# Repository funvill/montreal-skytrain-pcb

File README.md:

# montreal-skytrain-pcb

A printed circuit board that is a map of the Montréal Métro, with one
addressable RGB LED per station: all four lines plus the Blue line
extension to Anjou, 73 stations in all. A port of the
[Vancouver SkyTrain PCB](https://github.com/funvill/vancouver-skytrain-pcb).

**Sent to JLCPCB for manufacture on October 18th, 2026.** The files that
were uploaded are in [`manufactured/`](manufactured/)
(`jlcpcb_2026Oct18-191040.zip`, identical to the `2026-10-18-1853` outputs
in [`hardware/jlcpcb/`](hardware/jlcpcb/)).

**Front:** square 160 × 160 mm schematic map with straight lines and rounded
bends, exposed-copper (ENIG gold) water at true scale, silkscreen routes,
station rings and official station names, one XL-1615 WS2812B LED per
station.

**Back:** snowy owl in a tie, Seeed XIAO RP2040 controller (soldered by
hand), pads for four buttons, LED chain and power test points, M3 mounting
holes.

Renders are KiCad 10 `kicad-cli pcb render` output (`tools/render_board.py`).

## Where things are

| Folder | What |
|---|---|
| [`hardware/`](hardware/) | KiCad 10 project; [`hardware/README.md`](hardware/README.md) covers the board's state, regeneration and checks |
| [`hardware/jlcpcb/`](hardware/jlcpcb/) | Gerbers, BOM and pick-and-place for JLCPCB, and how they were made |
| [`manufactured/`](manufactured/) | The exact package sent to the manufacturer |
| [`input/`](input/) | Station and water data, the map builders, and the hand label placements |
| [`tools/`](tools/) | The pipeline: placement, artwork, labels, routing helpers, checks, outputs |
| [`firmware/`](firmware/) | XIAO RP2040 firmware with the STM line colours |
| [`runbook-new-city.md`](runbook-new-city.md) | How to port the board to another city |
| [`lessons-learned.md`](lessons-learned.md) | What this board and the Vancouver one taught, and the pre-order checklist |

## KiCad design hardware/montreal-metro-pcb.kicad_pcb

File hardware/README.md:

# Hardware (KiCad 10)

`montreal-metro-pcb` — 160 × 160 mm, 2 layers, 73 WS2812B LEDs (XL-1615), one
per station, generated from `../input/montreal-schematic-square.json`.

Copied from the Vancouver SkyTrain v3 project and ported by the scripts in
`../tools`. **The board is placed and has its artwork. It is not routed: routing is done by hand.**

## State

| | |
|---|---|
| Schematic | 73 LEDs. LED69–73 were added by `add_schematic_leds.py`; chain and power verified from KiCad's netlist by `check_led_chain.py` |
| Board vs schematic | 0 parity issues (`kicad-cli pcb drc --schematic-parity`) |
| Placement | LEDs at their stations, each turned so DOUT faces the next LED; 8 capacitors on the front in spots clear of labels, routes and water; XIAO and buttons on the back at (124, 122) mm, away from the downtown LEDs whose vias their pads would block; M3 holes 4 mm in from each corner |
| Bulk capacitor | `C1`, 100 µF 6.3 V X5R 1206 (LCSC C15008, a JLCPCB basic part), on the back at (140, 132.3) mm beside the +5V track from U1 pad 14 to the +5V2 test point. Basic parts have no 100–470 µF electrolytic; the only other basic 100 µF is a 6.3 V tantalum, which is too close to its rating on a 5 V rail. At 5 V the ceramic's DC-bias derating leaves roughly a quarter of its nominal value |
| Data line | `R1`, 330 Ω 0402 (LCSC C25104, basic), in series between U1 pad 8 (`LED_DATA`, also on the `LED_IN1` test point) and LED1 (`LED_IN`), on the front beside the data via at (130.4, 110.5) mm |
| Back artwork | Snowy owl in a tie (`../snowy_owl_tie_pcb_silkscreen.svg`) on B.SilkS as the board-only footprint `LOGO1`: 66.9 × 100 mm, centred, top 2/3 of the board, clear of every back-side part. Regenerate with `svg_to_silk.py` (below) |
| Artwork | Water (bare copper), routes, station rings and labels, wordmark — written by `export_art.py` |
| Labels | Placed by hand in KiCad (2026-10-13) and frozen in `../input/label_overrides-square.json`; every build re-applies them |
| Routing | **None.** The tracks are to be routed by hand. An autorouted version (Freerouting, DRC-clean) is in git history at `b02ee1b` for reference |
| DRC | No clearance, edge, short or courtyard violations; every net is unconnected until routed |
| Back side | The Vancouver moon-phase artwork was removed: it is 191 mm wide and does not fit this board |

## Regenerating

From `../tools`, after any change to the data file:

```
python export_placement.py ../input/montreal-schematic-square.json ../hardware --scale 2.0
python place_parts.py      ../input/montreal-schematic-square.json ../hardware --scale 2.0
python reposition_board.py ../hardware/montreal-metro-pcb.kicad_pcb ../hardware/leds.csv --board 160 --height 160 --controller 124 122
kicad-cli sch export netlist --format kicadsexpr -o ../test-results/netlist.net ../hardware/montreal-metro-pcb.kicad_sch
"C:/Program Files/KiCad/10.0/bin/python.exe" port_board.py ../hardware/montreal-metro-pcb.kicad_pcb ../test-results/netlist.net ../hardware/leds.csv ../hardware/parts.csv
python export_art.py       ../input/montreal-schematic-square.json ../hardware/montreal-metro-pcb.kicad_pcb --scale 2.0
"C:/Program Files/KiCad/10.0/bin/python.exe" mask_under_silk.py ../hardware/montreal-metro-pcb.kicad_pcb
```

Use the same `reposition_board.py` arguments every time, including
`--controller 124 122`.

`mask_under_silk.py` must follow every `export_art.py` run. The water is a
solder-mask opening, and silkscreen cannot print on an opening (JLCPCB clips
it, as does the gerber export's `--subtract-soldermask`), so the routes,
rings and leaders crossing the water would vanish. It closes the opening
0.2 mm around the ink; the copper stays, under mask.

## Routing

Routing is manual. The water is bare copper on the front with no net, so
front-side tracks must not cross it; ground pads on the front each need a
via to the back pour, because the front pour is cut into islands by the
artwork. `U1` pad 13 (GND) sits between two pads closer than the pour's
clearance, so the pour will not reach it: give it a track.

`rebuild_board.sh` leaves tracks alone. `rebuild_board.sh --autoroute`
replaces **every** track with the autorouter's (`autoroute.py`,
`stitch_ground.py`); `autoroute.py clear` removes them all.

## After editing labels in KiCad

```
python import_labels.py ../input/montreal-schematic-square.json ../hardware/montreal-metro-pcb.kicad_pcb
python save_label_overrides.py ../input/montreal-schematic-square.json ../input/label_overrides-square.json
```

Do this before any rebuild, or the exporter writes the old labels back.

`port_board.py` moves LEDs and re-aims them, so once tracks exist, re-running
it after moving a station will leave those tracks behind. Do not pass
`--strip` again: that removes every track and all front artwork.

Or run the whole thing, placement through renders, in one go (Git Bash, from
`../tools`); it does not touch tracks:

```
./rebuild_board.sh
```

## Back artwork

```
"C:/Program Files/KiCad/10.0/bin/python.exe" svg_to_silk.py ../snowy_owl_tie_pcb_silkscreen.svg ../hardware/montreal-metro-pcb.kicad_pcb --ref LOGO1 --height 100 --top 4.5
```

Replaces `LOGO1` in place; the art is mirrored so it reads correctly from the back.

## Checking

```
python check_led_chain.py ../test-results/netlist.net 73
kicad-cli pcb drc ../hardware/montreal-metro-pcb.kicad_pcb -o ../test-results/drc.json --format json --severity-error --severity-warning --schematic-parity --refill-zones --save-board
python render_board.py ../hardware/montreal-metro-pcb.kicad_pcb ../test-results --kicad-cli "C:/Program Files/KiCad/10.0/bin/kicad-cli.exe"
```

## Still to do

1. **Route the board** (by hand).
2. Check U1's orientation (USB-C toward a board edge) and the test-point
   positions on the back.
3. New back-side artwork, if wanted.
5. DRC, then fabrication outputs (`make_jlcpcb.py`). ENIG finish, so the bare
   copper reads gold.

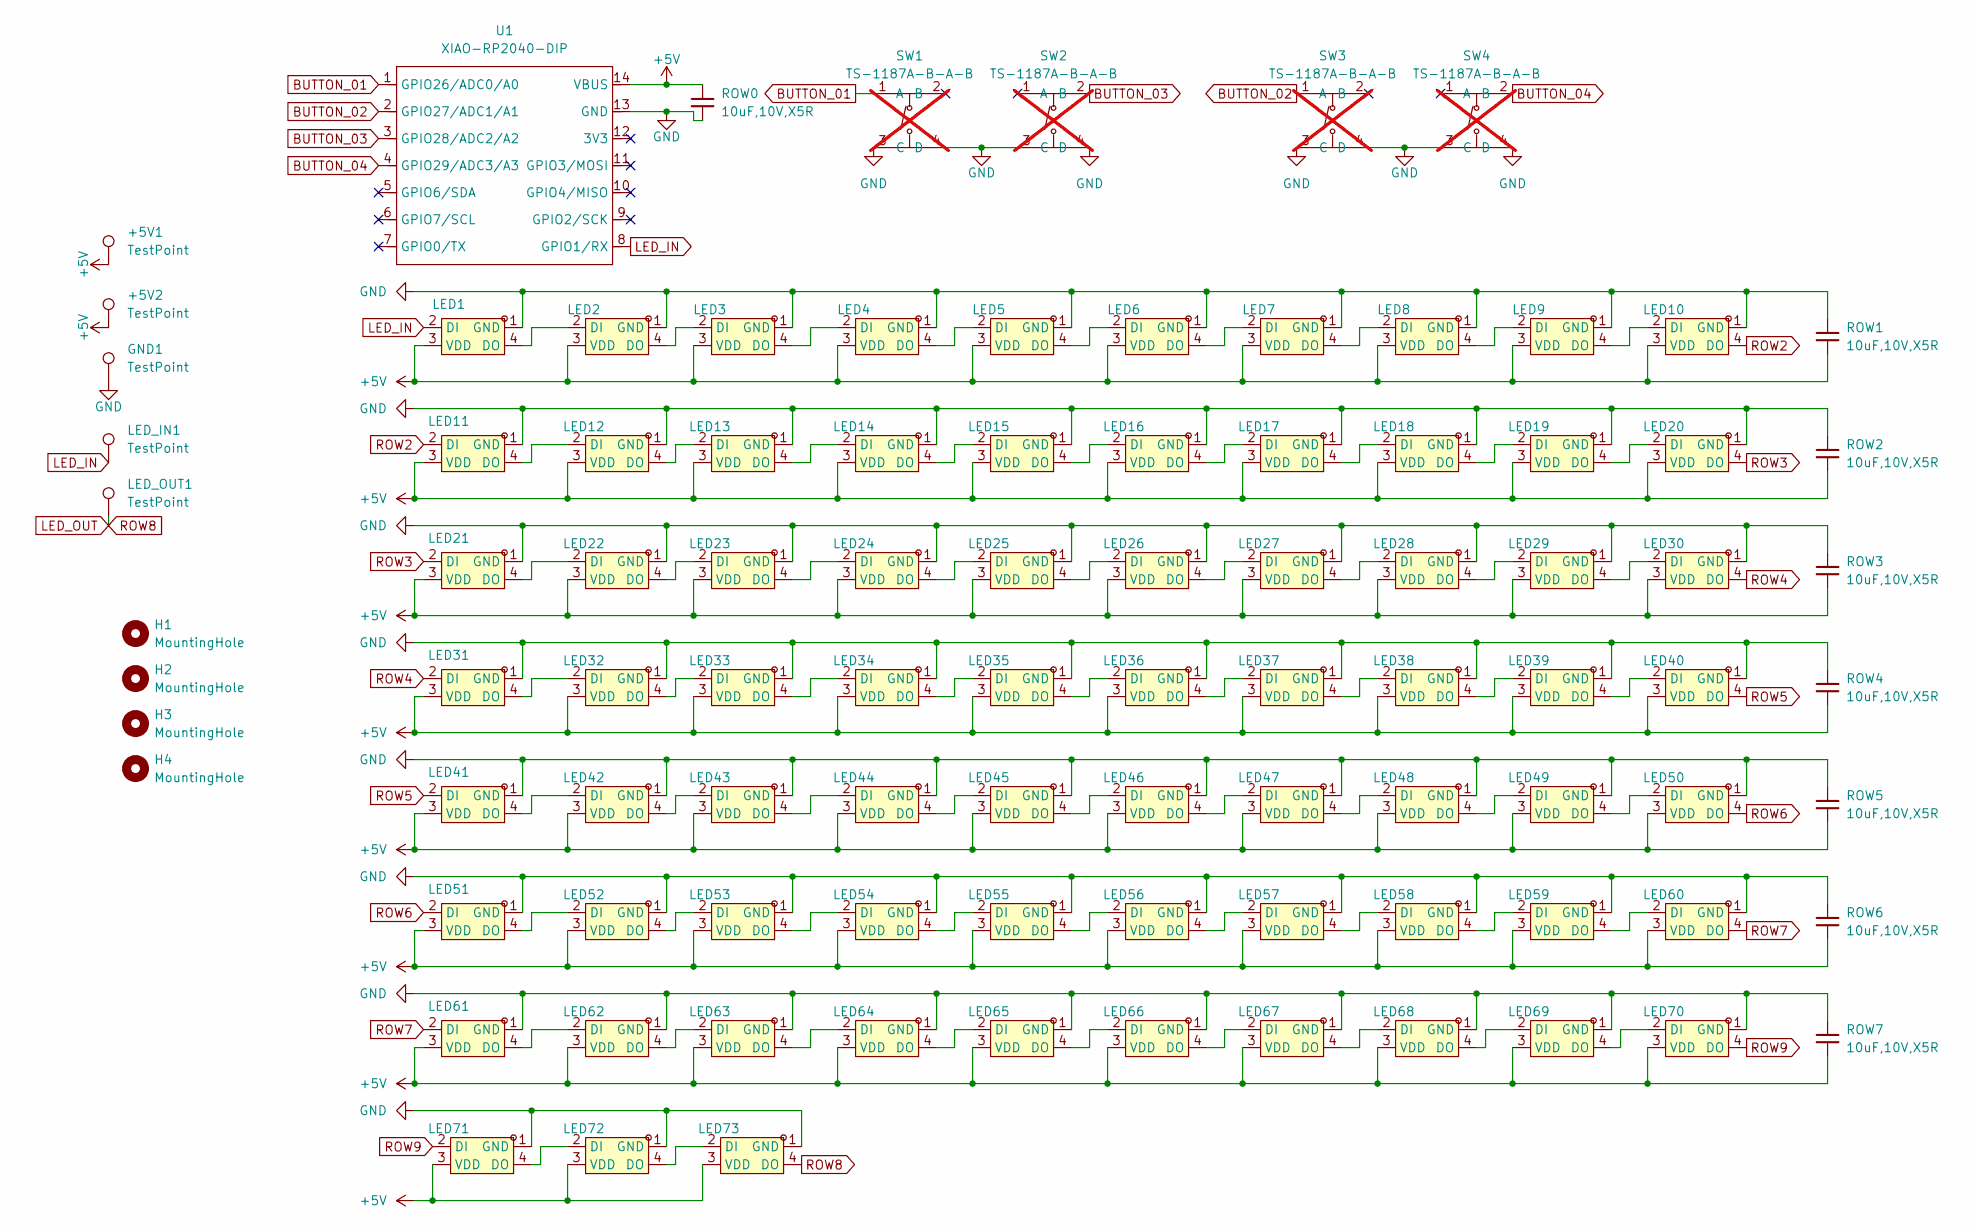
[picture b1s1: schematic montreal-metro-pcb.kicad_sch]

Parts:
+5V1, +5V2: TestPoint; TestPoint_Pad_3.0x3.0mm
GND1: TestPoint; TestPoint_Pad_3.0x3.0mm
H1, H2, H3, H4: MountingHole; MountingHole_3.2mm_M3_DIN965_Pad_TopBottom
LED1, LED2, LED3, LED4, LED5, LED6, LED7, LED8, LED9, LED10, LED11, LED12, LED13, LED14, LED15, LED16, LED17, LED18, LED19, LED20, LED21, LED22, LED23, LED24, LED25, LED26, LED27, LED28, LED29, LED30, LED31, LED32, LED33, LED34, LED35, LED36, LED37, LED38, LED39, LED40, LED41, LED42, LED43, LED44, LED45, LED46, LED47, LED48, LED49, LED50, LED51, LED52, LED53, LED54, LED55, LED56, LED57, LED58, LED59, LED60, LED61, LED62, LED63, LED64, LED65, LED66, LED67, LED68, LED69, LED70, LED71, LED72, LED73: XL-1615RGBC-WS2812B; LED-SMD_4P-L1.6-W1.5_XL-1615RGBC-WS2812B-1; LCSC Part C5349954
LED_IN1: TestPoint; TestPoint_Pad_3.0x3.0mm
LED_OUT1: TestPoint; TestPoint_Pad_3.0x3.0mm
ROW0, ROW1, ROW2, ROW3, ROW4, ROW5, ROW6, ROW7: 10uF,10V,X5R; C_0402_1005Metric; MFGPN CL05A105KA5NQNC; LCSC C52923
SW1, SW2, SW3, SW4: TS-1187A-B-A-B; SW-SMD_4P-L5.1-W5.1-P3.70-LS6.5-TL_H1.5; LCSC Part C318884; not fitted
U1: XIAO-RP2040-DIP; XIAO-RP2040-SMD

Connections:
+5V: +5V1.1 (1_1), +5V2.1 (1_1), LED1.3 (VDD), LED2.3 (VDD), LED3.3 (VDD), LED4.3 (VDD), LED5.3 (VDD), LED6.3 (VDD), LED7.3 (VDD), LED8.3 (VDD), LED9.3 (VDD), LED10.3 (VDD), LED11.3 (VDD), LED12.3 (VDD), LED13.3 (VDD), LED14.3 (VDD), LED15.3 (VDD), LED16.3 (VDD), LED17.3 (VDD), LED18.3 (VDD), LED19.3 (VDD), LED20.3 (VDD), LED21.3 (VDD), LED22.3 (VDD), LED23.3 (VDD), LED24.3 (VDD), LED25.3 (VDD), LED26.3 (VDD), LED27.3 (VDD), LED28.3 (VDD), LED29.3 (VDD), LED30.3 (VDD), LED31.3 (VDD), LED32.3 (VDD), LED33.3 (VDD), LED34.3 (VDD), LED35.3 (VDD), LED36.3 (VDD), LED37.3 (VDD), LED38.3 (VDD), LED39.3 (VDD), LED40.3 (VDD), LED41.3 (VDD), LED42.3 (VDD), LED43.3 (VDD), LED44.3 (VDD), LED45.3 (VDD), LED46.3 (VDD), LED47.3 (VDD), LED48.3 (VDD), LED49.3 (VDD), LED50.3 (VDD), LED51.3 (VDD), LED52.3 (VDD), LED53.3 (VDD), LED54.3 (VDD), LED55.3 (VDD), LED56.3 (VDD), LED57.3 (VDD), LED58.3 (VDD), LED59.3 (VDD), LED60.3 (VDD), LED61.3 (VDD), LED62.3 (VDD), LED63.3 (VDD), LED64.3 (VDD), LED65.3 (VDD), LED66.3 (VDD), LED67.3 (VDD), LED68.3 (VDD), LED69.3 (VDD), LED70.3 (VDD), LED71.3 (VDD), LED72.3 (VDD), LED73.3 (VDD), ROW0.1, ROW1.2, ROW2.2, ROW3.2, ROW4.2, ROW5.2, ROW6.2, ROW7.2, U1.14 (VBUS); also elsewhere on the board
BUTTON_01: SW1.1 (A), U1.1 (GPIO26/ADC0/A0); also elsewhere on the board
BUTTON_02: SW3.1 (A), U1.2 (GPIO27/ADC1/A1); also elsewhere on the board
BUTTON_03: SW2.2 (B), U1.3 (GPIO28/ADC2/A2); also elsewhere on the board
BUTTON_04: SW4.2 (B), U1.4 (GPIO29/ADC3/A3); also elsewhere on the board
GND: GND1.1 (1_1), LED1.1 (GND), LED2.1 (GND), LED3.1 (GND), LED4.1 (GND), LED5.1 (GND), LED6.1 (GND), LED7.1 (GND), LED8.1 (GND), LED9.1 (GND), LED10.1 (GND), LED11.1 (GND), LED12.1 (GND), LED13.1 (GND), LED14.1 (GND), LED15.1 (GND), LED16.1 (GND), LED17.1 (GND), LED18.1 (GND), LED19.1 (GND), LED20.1 (GND), LED21.1 (GND), LED22.1 (GND), LED23.1 (GND), LED24.1 (GND), LED25.1 (GND), LED26.1 (GND), LED27.1 (GND), LED28.1 (GND), LED29.1 (GND), LED30.1 (GND), LED31.1 (GND), LED32.1 (GND), LED33.1 (GND), LED34.1 (GND), LED35.1 (GND), LED36.1 (GND), LED37.1 (GND), LED38.1 (GND), LED39.1 (GND), LED40.1 (GND), LED41.1 (GND), LED42.1 (GND), LED43.1 (GND), LED44.1 (GND), LED45.1 (GND), LED46.1 (GND), LED47.1 (GND), LED48.1 (GND), LED49.1 (GND), LED50.1 (GND), LED51.1 (GND), LED52.1 (GND), LED53.1 (GND), LED54.1 (GND), LED55.1 (GND), LED56.1 (GND), LED57.1 (GND), LED58.1 (GND), LED59.1 (GND), LED60.1 (GND), LED61.1 (GND), LED62.1 (GND), LED63.1 (GND), LED64.1 (GND), LED65.1 (GND), LED66.1 (GND), LED67.1 (GND), LED68.1 (GND), LED69.1 (GND), LED70.1 (GND), LED71.1 (GND), LED72.1 (GND), LED73.1 (GND), ROW0.2, ROW1.1, ROW2.1, ROW3.1, ROW4.1, ROW5.1, ROW6.1, ROW7.1, SW1.3 (C), SW1.4 (D), SW2.3 (C), SW2.4 (D), SW3.3 (C), SW3.4 (D), SW4.3 (C), SW4.4 (D), U1.13 (GND); also elsewhere on the board
LED_OUT: LED73.4 (DO), LED_OUT1.1 (1_1)
unnamed: LED1.4 (DO), LED2.2 (DI)
unnamed: LED2.4 (DO), LED3.2 (DI)
unnamed: LED3.4 (DO), LED4.2 (DI)
unnamed: LED4.4 (DO), LED5.2 (DI)
unnamed: LED5.4 (DO), LED6.2 (DI)
unnamed: LED6.4 (DO), LED7.2 (DI)
unnamed: LED7.4 (DO), LED8.2 (DI)
unnamed: LED8.4 (DO), LED9.2 (DI)
unnamed: LED9.4 (DO), LED10.2 (DI)
unnamed: LED11.4 (DO), LED12.2 (DI)
unnamed: LED12.4 (DO), LED13.2 (DI)
unnamed: LED13.4 (DO), LED14.2 (DI)
unnamed: LED14.4 (DO), LED15.2 (DI)
unnamed: LED15.4 (DO), LED16.2 (DI)
unnamed: LED16.4 (DO), LED17.2 (DI)
unnamed: LED17.4 (DO), LED18.2 (DI)
unnamed: LED18.4 (DO), LED19.2 (DI)
unnamed: LED19.4 (DO), LED20.2 (DI)
unnamed: LED21.4 (DO), LED22.2 (DI)
unnamed: LED22.4 (DO), LED23.2 (DI)
unnamed: LED23.4 (DO), LED24.2 (DI)
unnamed: LED24.4 (DO), LED25.2 (DI)
unnamed: LED25.4 (DO), LED26.2 (DI)
unnamed: LED26.4 (DO), LED27.2 (DI)
unnamed: LED27.4 (DO), LED28.2 (DI)
unnamed: LED28.4 (DO), LED29.2 (DI)
unnamed: LED29.4 (DO), LED30.2 (DI)
unnamed: LED31.4 (DO), LED32.2 (DI)
unnamed: LED32.4 (DO), LED33.2 (DI)
unnamed: LED33.4 (DO), LED34.2 (DI)
unnamed: LED34.4 (DO), LED35.2 (DI)
unnamed: LED35.4 (DO), LED36.2 (DI)
unnamed: LED36.4 (DO), LED37.2 (DI)
unnamed: LED37.4 (DO), LED38.2 (DI)
unnamed: LED38.4 (DO), LED39.2 (DI)
unnamed: LED39.4 (DO), LED40.2 (DI)
unnamed: LED41.4 (DO), LED42.2 (DI)
unnamed: LED42.4 (DO), LED43.2 (DI)
unnamed: LED43.4 (DO), LED44.2 (DI)
unnamed: LED44.4 (DO), LED45.2 (DI)
unnamed: LED45.4 (DO), LED46.2 (DI)
unnamed: LED46.4 (DO), LED47.2 (DI)
unnamed: LED47.4 (DO), LED48.2 (DI)
unnamed: LED48.4 (DO), LED49.2 (DI)
unnamed: LED49.4 (DO), LED50.2 (DI)
unnamed: LED51.4 (DO), LED52.2 (DI)
unnamed: LED52.4 (DO), LED53.2 (DI)
unnamed: LED53.4 (DO), LED54.2 (DI)
unnamed: LED54.4 (DO), LED55.2 (DI)
unnamed: LED55.4 (DO), LED56.2 (DI)
unnamed: LED56.4 (DO), LED57.2 (DI)
unnamed: LED57.4 (DO), LED58.2 (DI)
unnamed: LED58.4 (DO), LED59.2 (DI)
unnamed: LED59.4 (DO), LED60.2 (DI)
unnamed: LED61.4 (DO), LED62.2 (DI)
unnamed: LED62.4 (DO), LED63.2 (DI)
unnamed: LED63.4 (DO), LED64.2 (DI)
unnamed: LED64.4 (DO), LED65.2 (DI)
unnamed: LED65.4 (DO), LED66.2 (DI)
unnamed: LED66.4 (DO), LED67.2 (DI)
unnamed: LED67.4 (DO), LED68.2 (DI)
unnamed: LED68.4 (DO), LED69.2 (DI)
unnamed: LED69.4 (DO), LED70.2 (DI)
unnamed: LED71.4 (DO), LED72.2 (DI)
unnamed: LED72.4 (DO), LED73.2 (DI)
ROW2: LED10.4 (DO), LED11.2 (DI)
ROW3: LED20.4 (DO), LED21.2 (DI)
ROW4: LED30.4 (DO), LED31.2 (DI)
ROW5: LED40.4 (DO), LED41.2 (DI)
ROW6: LED50.4 (DO), LED51.2 (DI)
ROW7: LED60.4 (DO), LED61.2 (DI)
ROW9: LED70.4 (DO), LED71.2 (DI)

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
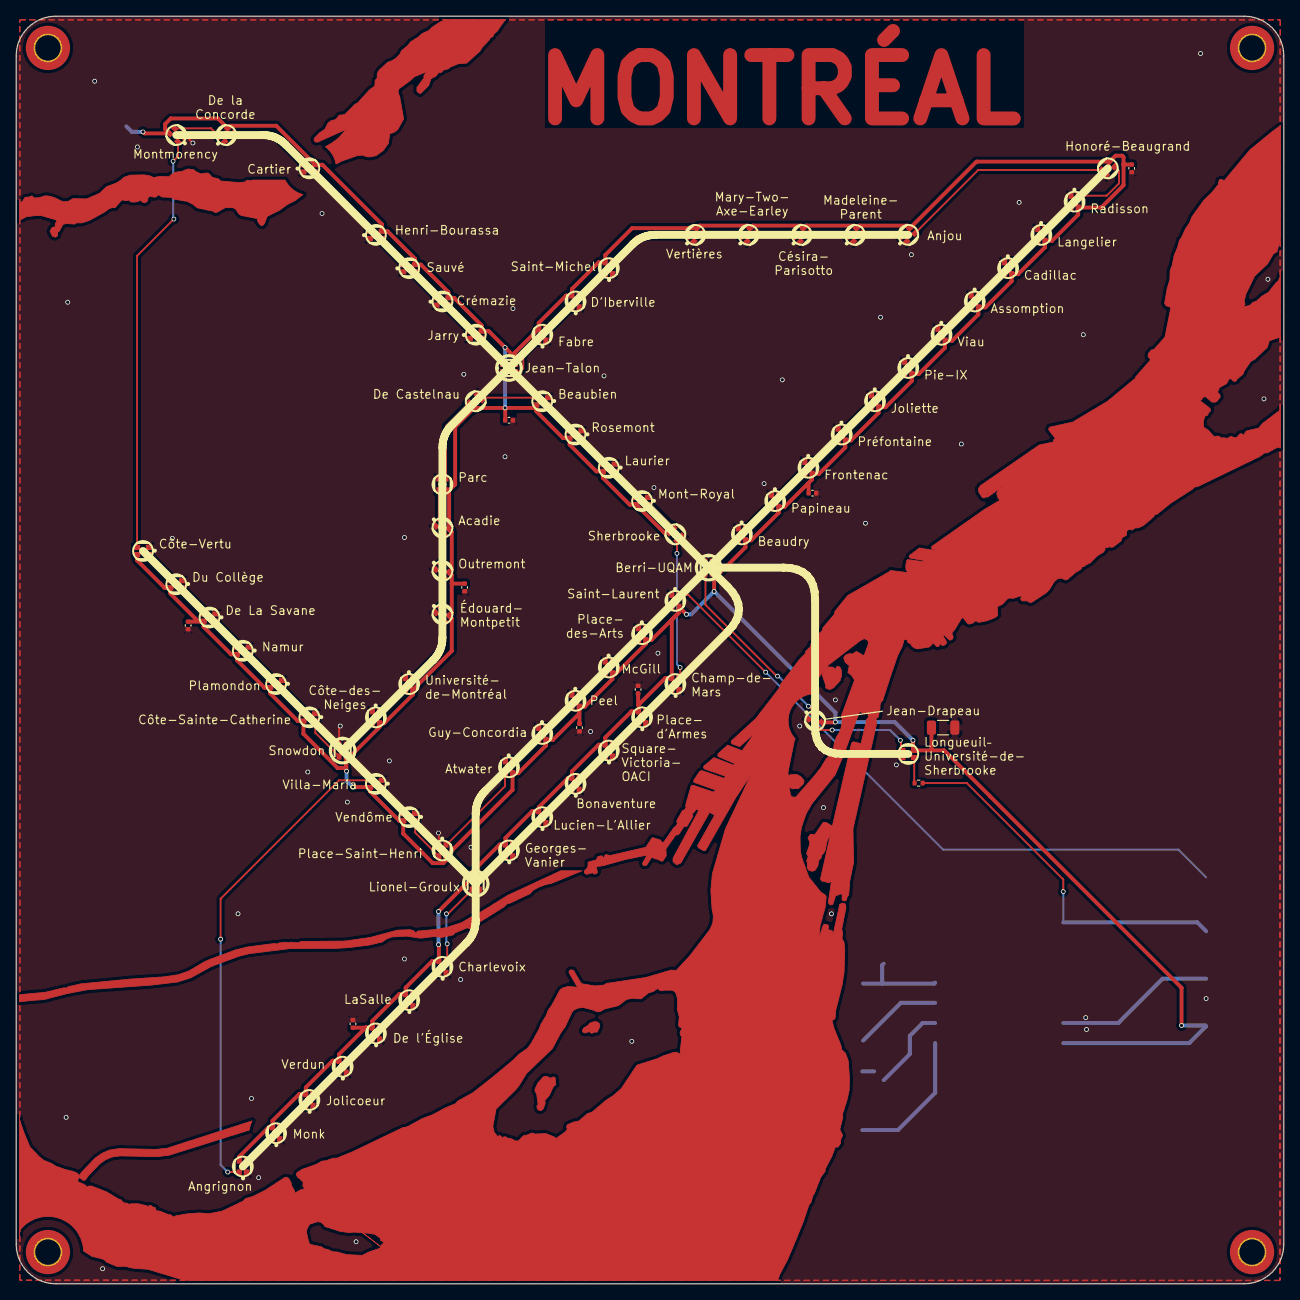
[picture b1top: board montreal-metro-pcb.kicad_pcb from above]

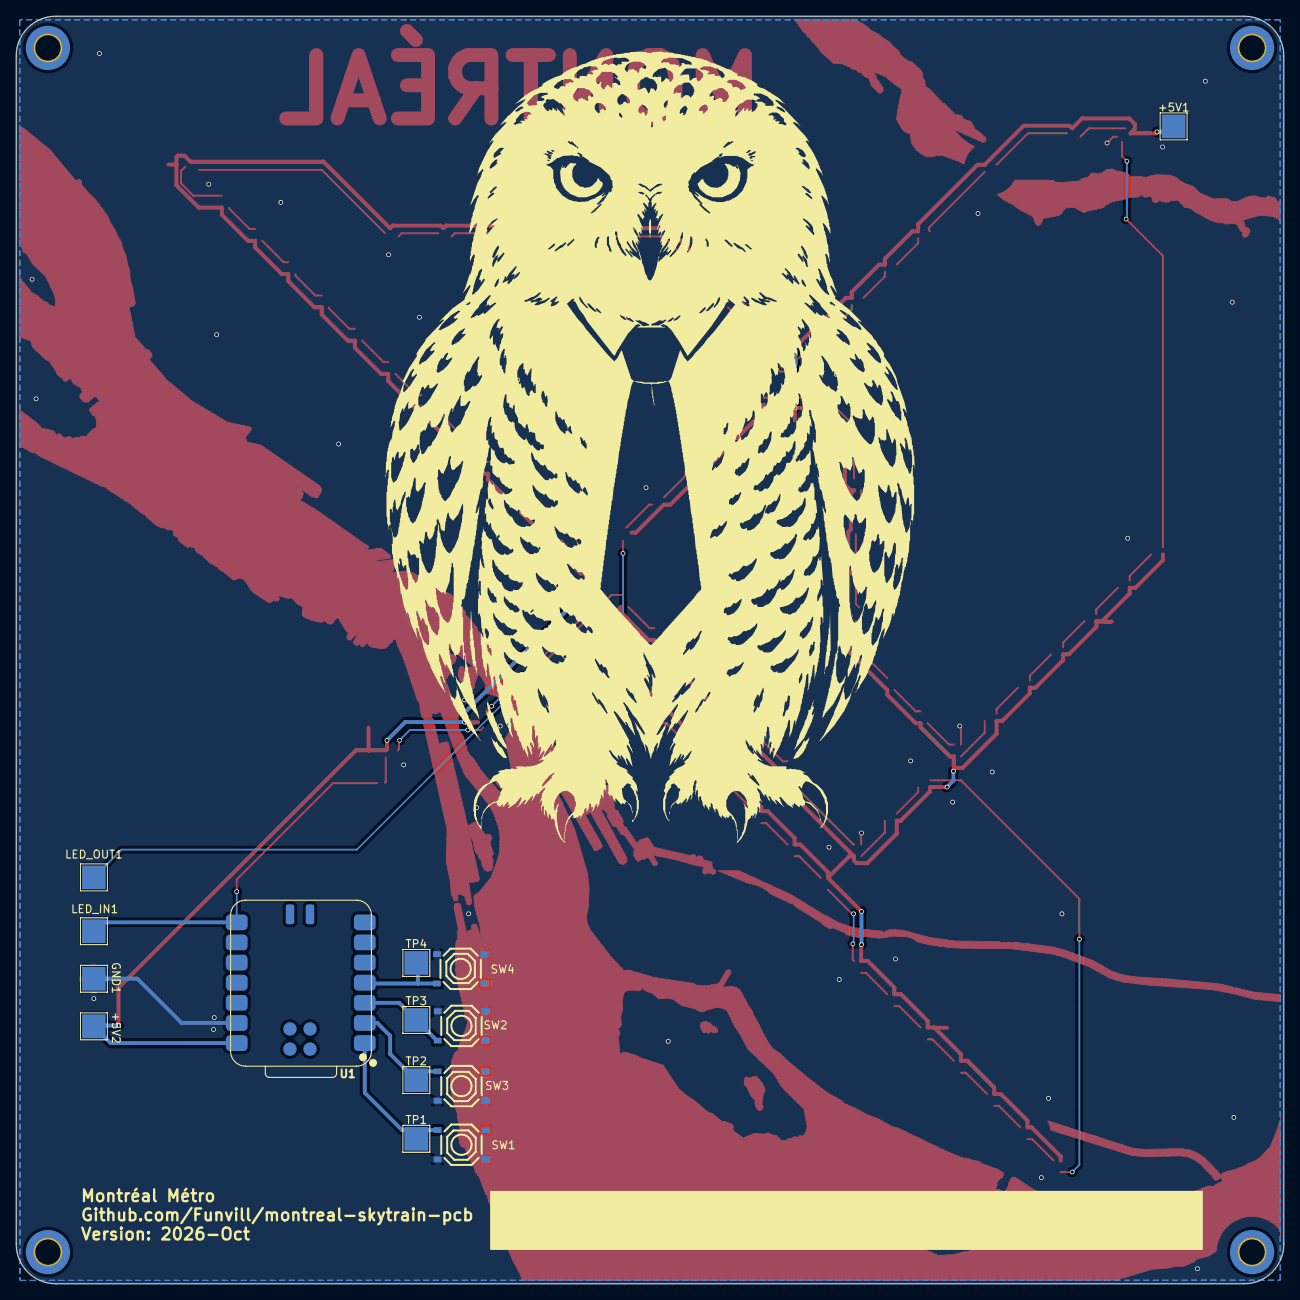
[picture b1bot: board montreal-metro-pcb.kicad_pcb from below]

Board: 2 copper layers, 160.0 x 160.0 mm, 102 parts (15 on the bottom side), 81 nets.

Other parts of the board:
C1: 100uF,6.3V,X5R; C_1206_3216Metric
LOGO1: artwork
R1: 330R; R_0402_1005Metric
TP1, TP2, TP3, TP4: TestPoint; TestPoint_Pad_3.0x3.0mm

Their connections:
+5V: C1.1; also elsewhere on the board
BUTTON_01: TP1.1 (1_1); also elsewhere on the board
BUTTON_02: TP2.1 (1_1); also elsewhere on the board
BUTTON_03: TP3.1 (1_1); also elsewhere on the board
BUTTON_04: TP4.1 (1_1); also elsewhere on the board
GND: C1.2; also elsewhere on the board
